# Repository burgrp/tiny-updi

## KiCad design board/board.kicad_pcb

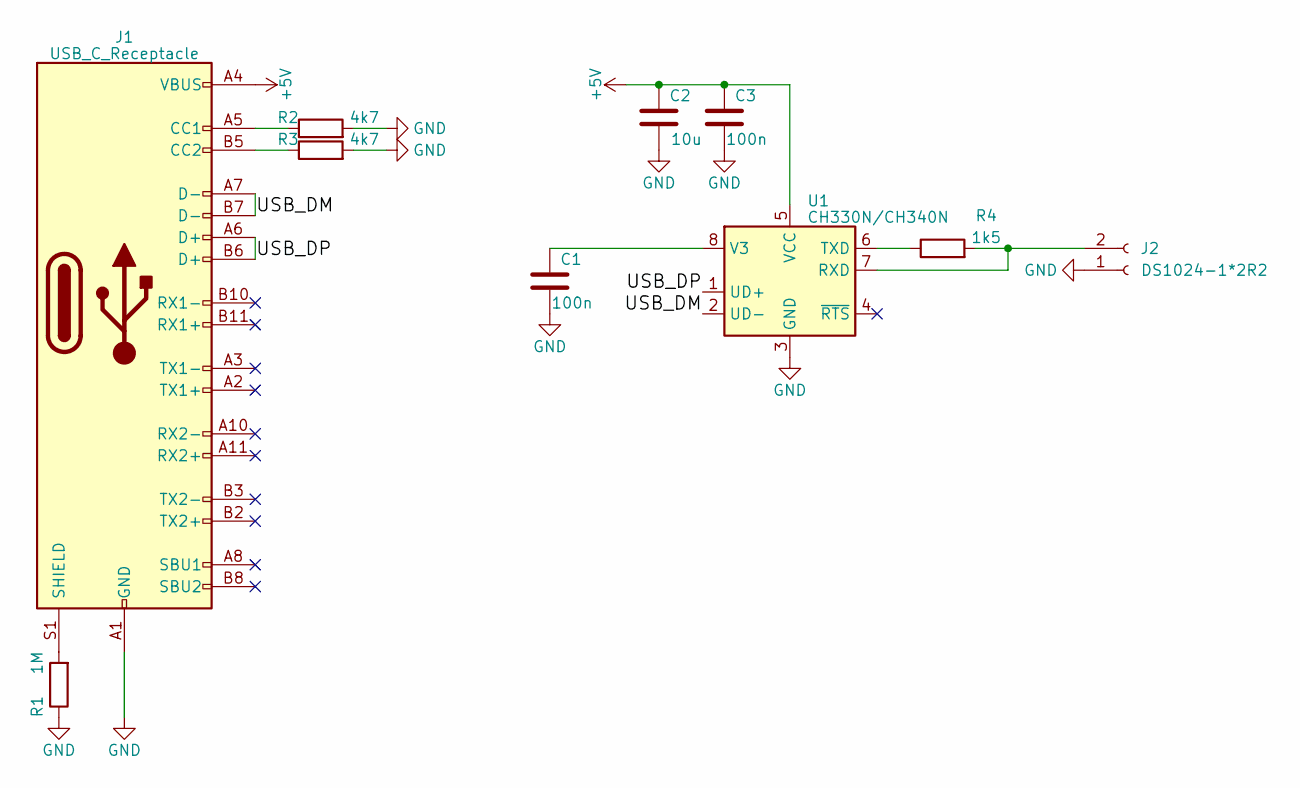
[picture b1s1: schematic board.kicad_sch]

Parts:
C1, C3: 100n; C_0805_2012Metric
C2: 10u; C_0805_2012Metric
J1: USB_C_Receptacle; USB_C_Receptacle-Handsolder
J2: DS1024-1*2R2; PinSocket_1x02_P2.54mm_Horizontal
R1: 1M; R_0805_2012Metric
R2, R3: 4k7; R_0805_2012Metric
R4: 1k5; R_0805_2012Metric
U1: CH330N/CH340N; SOIC-8_3.9x4.9mm_P1.27mm

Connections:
+5V: C2.2, C3.2, J1.A4 (VBUS), J1.A9 (VBUS), J1.B4 (VBUS), J1.B9 (VBUS), U1.5 (VCC)
/USB_DM: J1.A7 (D-), J1.B7 (D-), U1.2 (UD-)
/USB_DP: J1.A6 (D+), J1.B6 (D+), U1.1 (UD+)
GND: C1.1, C2.1, C3.1, J1.A1 (GND), J1.A12 (GND), J1.B1 (GND), J1.B12 (GND), J2.1, R1.1, R2.2, R3.2, U1.3 (GND)
unnamed: J1.A5 (CC1), R2.1
unnamed: J1.B5 (CC2), R3.1
unnamed: J1.S1 (SHIELD), R1.2
unnamed: J2.2, R4.2, U1.7 (RXD)
unnamed: R4.1, U1.6 (TXD)
unnamed: C1.2, U1.8 (V3)

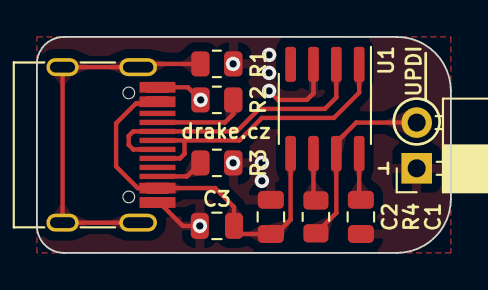
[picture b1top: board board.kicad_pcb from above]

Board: 2 copper layers, 23.0 x 12.0 mm, 10 parts (0 on the bottom side), 10 nets.

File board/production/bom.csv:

Designator,Footprint,Quantity,Value,LCSC Part #
C1,0805,1,100n,
C2,0805,1,10u,
C3,0805,1,100n,
J1,USB_C_Receptacle-Handsolder,1,USB_C_Receptacle,
J2,PinSocket_1x02_P2.54mm_Horizontal,1,DS1024-1*2R2,
R1,0805,1,1M,
R2,0805,1,4k7,
R3,0805,1,4k7,
R4,0805,1,1k5,
U1,SOIC-8_3.9x4.9mm_P1.27mm,1,CH330N/CH340N,
